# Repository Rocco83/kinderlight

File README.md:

# KinderLight RGB

KinderLight RGB is a smart night light based on an ESP32-C6 microcontroller,
capable of automatically adjusting brightness and color based on ambient light using a BH1750 sensor.

Designed to integrate natively with **Home Assistant** via **ESPHome**.

---

## Features

- Automatic ambient light detection with BH1750 sensor.
- RGB LED control via PWM (independent channels for Red, Green, Blue).
- Wi-Fi control and OTA (Over The Air) firmware updates.
- Web server interface for local diagnostics.
- Optional manual serial debug connection via JST-SH 5P or Tag-Connect footprint (future).
- Easy snap-in mount inside a **Vimar Plana** 14041 cover plate.
- Input voltage 7–24V regulated to 5V with buck converter.
- Smooth fade-in and fade-out effects.
- Automatic activation from sunset to sunrise (future).

## Hardware Required

- ESP32-C6 Supermini
- BH1750 light sensor module
- MP1584 DC-DC Stepdown Module
- RGB LED (common anode)
- 3D printed snap-in panel for Vimar 14041
- optionally, the PCB to host the components, otherwise replicate the same BOM

## Software

- ESPHome (latest)
- Home Assistant (latest)
- YAML automations provided.

## Installation

1. Flash the ESP32 using provided `kinderlight.yaml` ESPHome config.
2. Install the snap-in panel inside a Vimar 14041 (or custom box).
3. Wire the RGB LED and the BH1750 sensor
4. Upload automations to Home Assistant.

## Configuration

Lux table:
0.0 - 2.0 lx: Danger Zone (High risk of tripping/hitting furniture).
2.0 - 5.0 lx: Deep Twilight (Silhouettes only; no colors or textures visible).
5.0 - 10.0 lx: Twilight (General shapes visible; fine details are lost).
10.0 - 15.0 lx: Low Orientation (Safe to move; colors begin to be distinguishable).
15.0 - 20.0 lx: Dim Orientation (Comfortable for a nightlight; eye starts to adapt).
20.0 - 30.0 lx: Gloomy Interior (Environment feels "dark" but fully visible).

## Entities Created

- `light.kinderlight_rgb`
- `sensor.ambient_light_lux`

(Optional Voltage monitor if configured.)

## Automation Logic

- Turns on at sunset, off at sunrise.
- During daytime, activates if ambient lux falls below threshold.
- Full color control from Home Assistant dashboard.

## Future Plans

- Support for multiple KinderLights via groups.
- Additional effects (color cycling, breathing mode).

## License

GPL-3.0 License

---

## Project Structure

```plaintext
kinderlight_rgb/
├── README.md
├── LICENSE
├── hardware/
│   └── 3d_models/
│       ├── snapin_14041.stl
│       └── 
├── firmware/
│   ├── kinderlight_rgb.yaml
│   ├── example_automation.yaml
├── bom/
│   ├── bom_front.csv
│   ├── bom_rear.csv
└── tools/
    ├── wiring_diagram.svg
    └── wiring_diagram.png

## Backlog

MP1584 dimensions for kicad has been taken from:

https://components101.com/modules/mini-mp1584-dc-dc-3a-adjustable-buck-module

[docs/MP1584-Dimensions.png]
[docs/MP1584-Pinout.jpg]

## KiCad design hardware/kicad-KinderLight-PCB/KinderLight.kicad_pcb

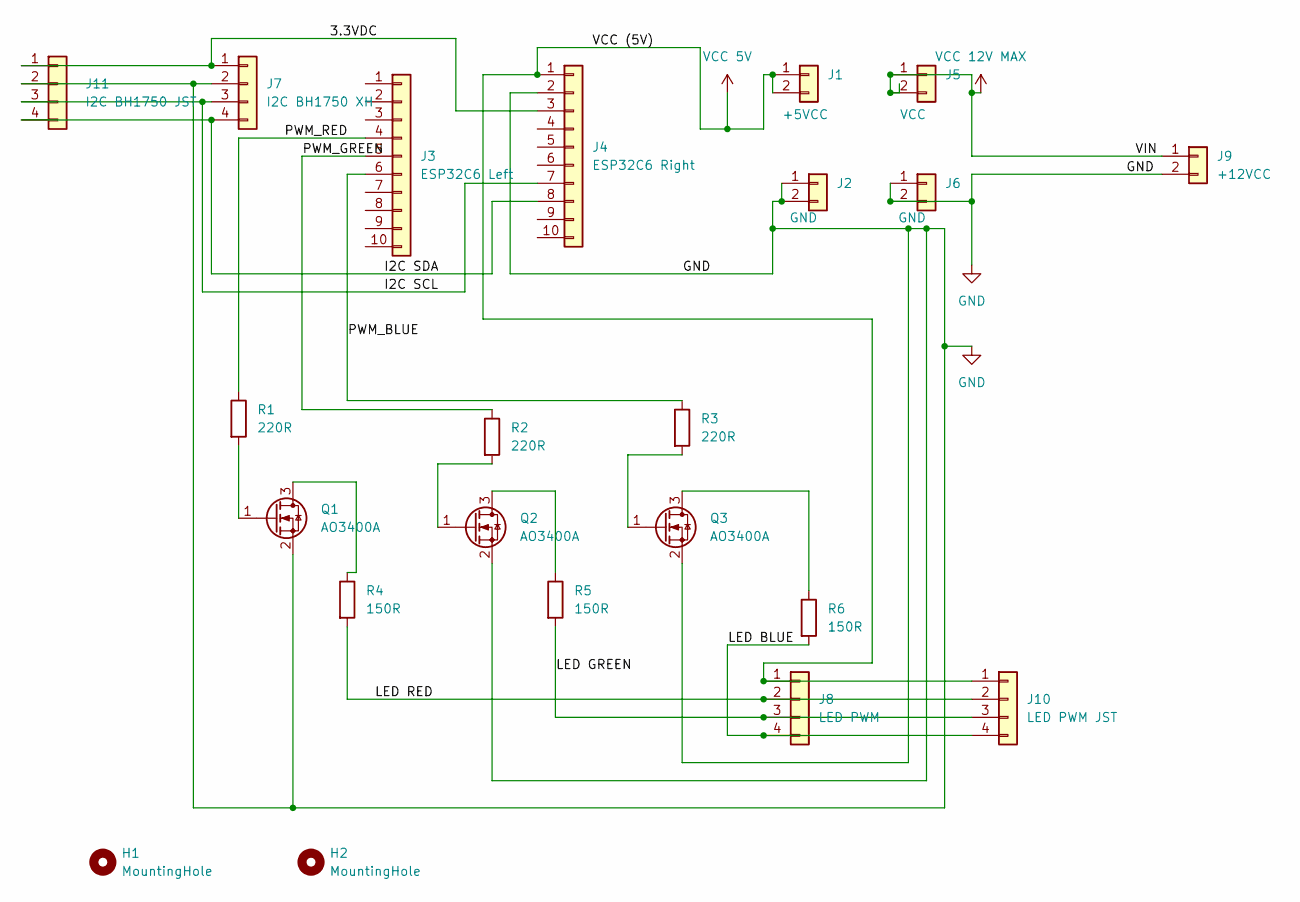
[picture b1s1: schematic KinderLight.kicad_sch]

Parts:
H1, H2: MountingHole; MountingHole_3.2mm_M3
J1: +5VCC; PinSocket_1x02_P2.54mm_Vertical
J2, J6: GND; PinSocket_1x02_P2.54mm_Vertical
J3: ESP32C6 Left; PinSocket_1x10_P2.54mm_Vertical
J4: ESP32C6 Right; PinSocket_1x10_P2.54mm_Vertical
J5: VCC; PinSocket_1x02_P2.54mm_Vertical
J7: I2C BH1750 XH; JST_XH_B4B-XH-AM_1x04_P2.50mm_Vertical; LCSC C161871
J8: LED PWM; JST_XH_B4B-XH-AM_1x04_P2.50mm_Vertical; LCSC C161871
J9: +12VCC; TerminalBlock_Phoenix_MKDS-1,5-2-5.08_1x02_P5.08mm_Horizont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; LCSC C22397914
J10: LED PWM JST; JST_PH_B4B-PH-K_1x04_P2.00mm_Vertical; LCSC C131334
J11: I2C BH1750 JST; JST_PH_B4B-PH-K_1x04_P2.00mm_Vertical; LCSC C131334
Q1, Q2, Q3: AO3400A; SOT-23; LCSC C20917
R1, R2, R3: 220R; R_0805_2012Metric; LCSC C17557
R4, R5, R6: 150R; R_0805_2012Metric; LCSC C17471

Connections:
/3.3VDC: J4.3, J7.1, J11.1
/I2C SCL: J4.7, J7.3, J11.3
/I2C SDA: J4.8, J7.4, J11.4
/LED BLUE: J8.4, J10.4, R6.2
/LED GREEN: J8.3, J10.3, R5.2
/LED RED: J8.2, J10.2, R4.2
/PWM_BLUE: J3.6, R3.1
/PWM_GREEN: J3.5, R2.1
/PWM_RED: J3.4, R1.1
GND: J2.1, J2.2, J4.2, J6.1, J6.2, J7.2, J9.2, J11.2, Q1.2 (S), Q2.2 (S), Q3.2 (S)
unnamed: Q1.3 (D), R4.1
unnamed: Q1.1 (G), R1.2
unnamed: Q2.3 (D), R5.1
unnamed: Q2.1 (G), R2.2
unnamed: Q3.3 (D), R6.1
unnamed: Q3.1 (G), R3.2
VCC 5V: J1.1, J1.2, J4.1, J8.1, J10.1
VCC 12V MAX: J5.1, J5.2, J9.1

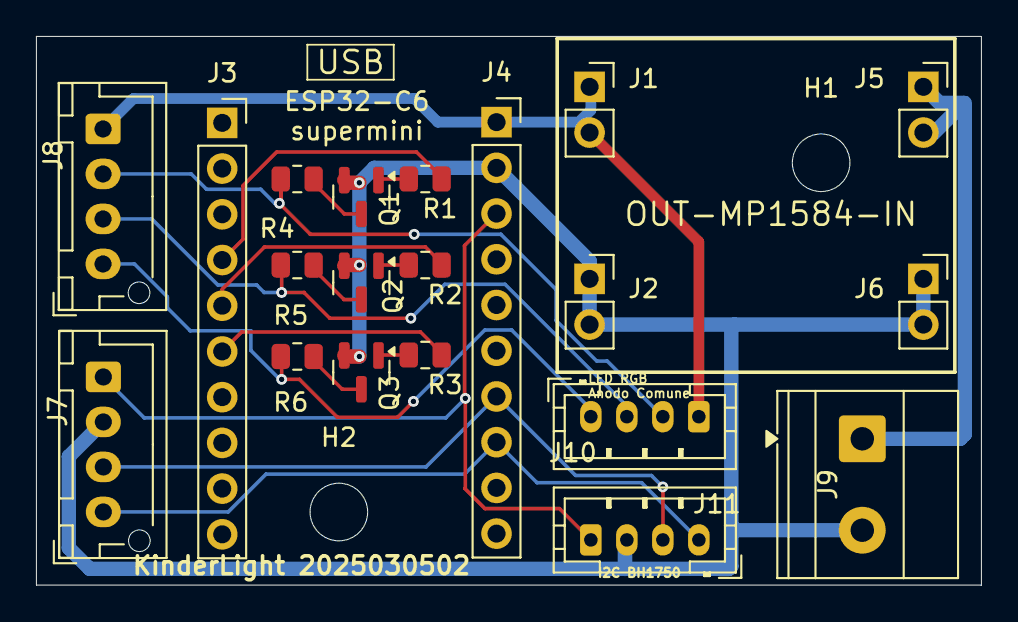
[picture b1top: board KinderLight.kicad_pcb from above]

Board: 2 copper layers, 52.5 x 30.5 mm, 22 parts (0 on the bottom side), 18 nets.

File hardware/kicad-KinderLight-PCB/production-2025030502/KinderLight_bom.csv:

Designator,Footprint,Quantity,Value,LCSC Part #
J1,PinSocket_1x02_P2.54mm_Vertical,1,+5VCC,
J10,JST_PH_B4B-PH-K_1x04_P2.00mm_Vertical,1,LED PWM JST,C131334
J11,JST_PH_B4B-PH-K_1x04_P2.00mm_Vertical,1,I2C BH1750 JST,C131334
"J2, J6",PinSocket_1x02_P2.54mm_Vertical,2,GND,
J3,PinSocket_1x10_P2.54mm_Vertical,1,ESP32C6 Left,
J4,PinSocket_1x10_P2.54mm_Vertical,1,ESP32C6 Right,
J5,PinSocket_1x02_P2.54mm_Vertical,1,VCC,
J7,JST_XH_B4B-XH-AM_1x04_P2.50mm_Vertical,1,I2C BH1750 XH,C161871
J8,JST_XH_B4B-XH-AM_1x04_P2.50mm_Vertical,1,LED PWM,C161871
J9,"TerminalBlock_Phoenix_MKDS-1,5-2-5.08_1x02_P5.08mm_Horizontal",1,+12VCC,C22397914
"Q1, Q2, Q3",SOT-23,3,AO3400A,C20917
"R1, R2, R3",0805,3,220R,C17557
"R4, R5, R6",0805,3,150R,C17471

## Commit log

2025-05-10 review needed for firmware
2025-05-11 fixed firmware
    merged & removed v2 and v3 code
    modified gitignore to skip secrets.yaml
    edited the pin in use
    merged & removed sidecars files
2025-12-19 Code cleanup, major changes
    - added sliders per color
    - upgraded to web server v3 for color selection in the palette
    - added diagnostic logs
    - added two SSID support (multi-home)
    - code cleanup
    - other changes that went untracked ...
2025-12-27 Prod 1.0
    Removed day change of light - commented
    Added button for reset of memory - when the sliders are missing, in example
2025-12-27 v2 - still to be confirmed
2025-12-28 first test snapin
2025-12-28 lowered time for debug purpose
2025-12-28 removed old hardware, added kicad
2025-12-28 review docs & removed unneeded files
2026-01-09 test version for the scad file
2026-01-11 rev3 scad file
2026-01-11 removed the snaps (unused)
2026-01-11 fixed the width to be parametric
    This is now based on the internal width, easier to be calculated
2026-01-11 added test stl
2026-01-20 removed unused openscad code, reverted to fn=200
2026-01-24 fix & print
2026-01-24 removed unused file
2026-01-24 Version 20260124v2
    version v1 (no v) differ from groove height
2026-02-01 3d version 20260131
    - fixed dimensions for adapting the print
    - added a lager led holder seat on the top
2026-02-02 Beta 1.0
    Removed unused files
    in the esphome file
    - enforced the esp-idf framework
    - added a multiplier in case of the reading of the sensor is off target
    - moved to text instead of sliders the single colors of the RGB
    - added a default value of 100 for the single textbox
2026-02-02 Added mising icon, moved "is_dark" to diagnostic
2026-02-02 Beta 2.0
    - Improved the automatic calculation
    - removed obsolete code
    - moved some buttons around config and diagnostic
2026-02-02 Added the auto calculation of the "light back"
2026-02-02 Excluded .platformio/ from the list of tracked files
2026-02-02 Sensor multiplier and calibration fix
    The sensor multiplier is not fixed to 1 anymore
    It has a default of x2 (based on empiric test on Plana 14041 as by 3d model)
    Also, the values are visible in diagnostic.
    In the calibration the time has been moved from 3s to 5s
    In 3 seconds the light sensor is still assessing the proper value.
2026-02-02 Added lux mapping in readme
2026-02-02 Refined the calibration, fixed the initial bright
    The calibration was not turning off the manual override - to avoid flapping
    The initial brightness of the RGB led should be 50%
2026-02-08 Added MP1584 pinout & dimensions
2026-02-08 Added pictures for README
2026-02-08 Added version 20260207 of the PCB
2026-02-08 Added reboot button
2026-03-06 WiFi improvements
    WiFi was stable but not working. This has been solved at AP side.
    Anyhow, some improgements has been done in the code.
    - added a debug on the WiFi signal in the log
    - implemented post_connect_roaming
    - moved the limit from -80dB to -90dB
2026-03-06 Added production version of the snapin
    This is the version printed in the main batch
2026-03-06 removal of old gerber and production files
2026-03-06 removal of the old stl file - never produced
2026-03-06 removed another gerber file
2026-03-06 Added the production file for the PCB sent
2026-03-06 Added the kicad source file of the production batch
2026-03-06 .gitignore updated
2026-03-06 Fixed .gitignore and removed the cache fp-info-cache
2026-03-06 Added ledholder breakout, renamed kicad main pcb
2026-03-06 First beta for the PCB box - NOT correct
2026-04-04 Added the last calibration time and fixed defaults
    The new last calibration time has been added
    The default values has been changed to reflect
    - the default lux threshort
    - the default calibration map
